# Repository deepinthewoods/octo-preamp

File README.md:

# PCB boards

This repository contains schematics and boards built using the `pcb` command line utility by Diode, using the Zener language and open source compiler

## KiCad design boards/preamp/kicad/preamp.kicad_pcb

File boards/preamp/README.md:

# preamp

## Description

<!-- Brief description of this board -->

## Features

-

## Build Instructions

```bash
pcb build boards/preamp
pcb layout boards/preamp
```

## License

<!-- Add license information -->

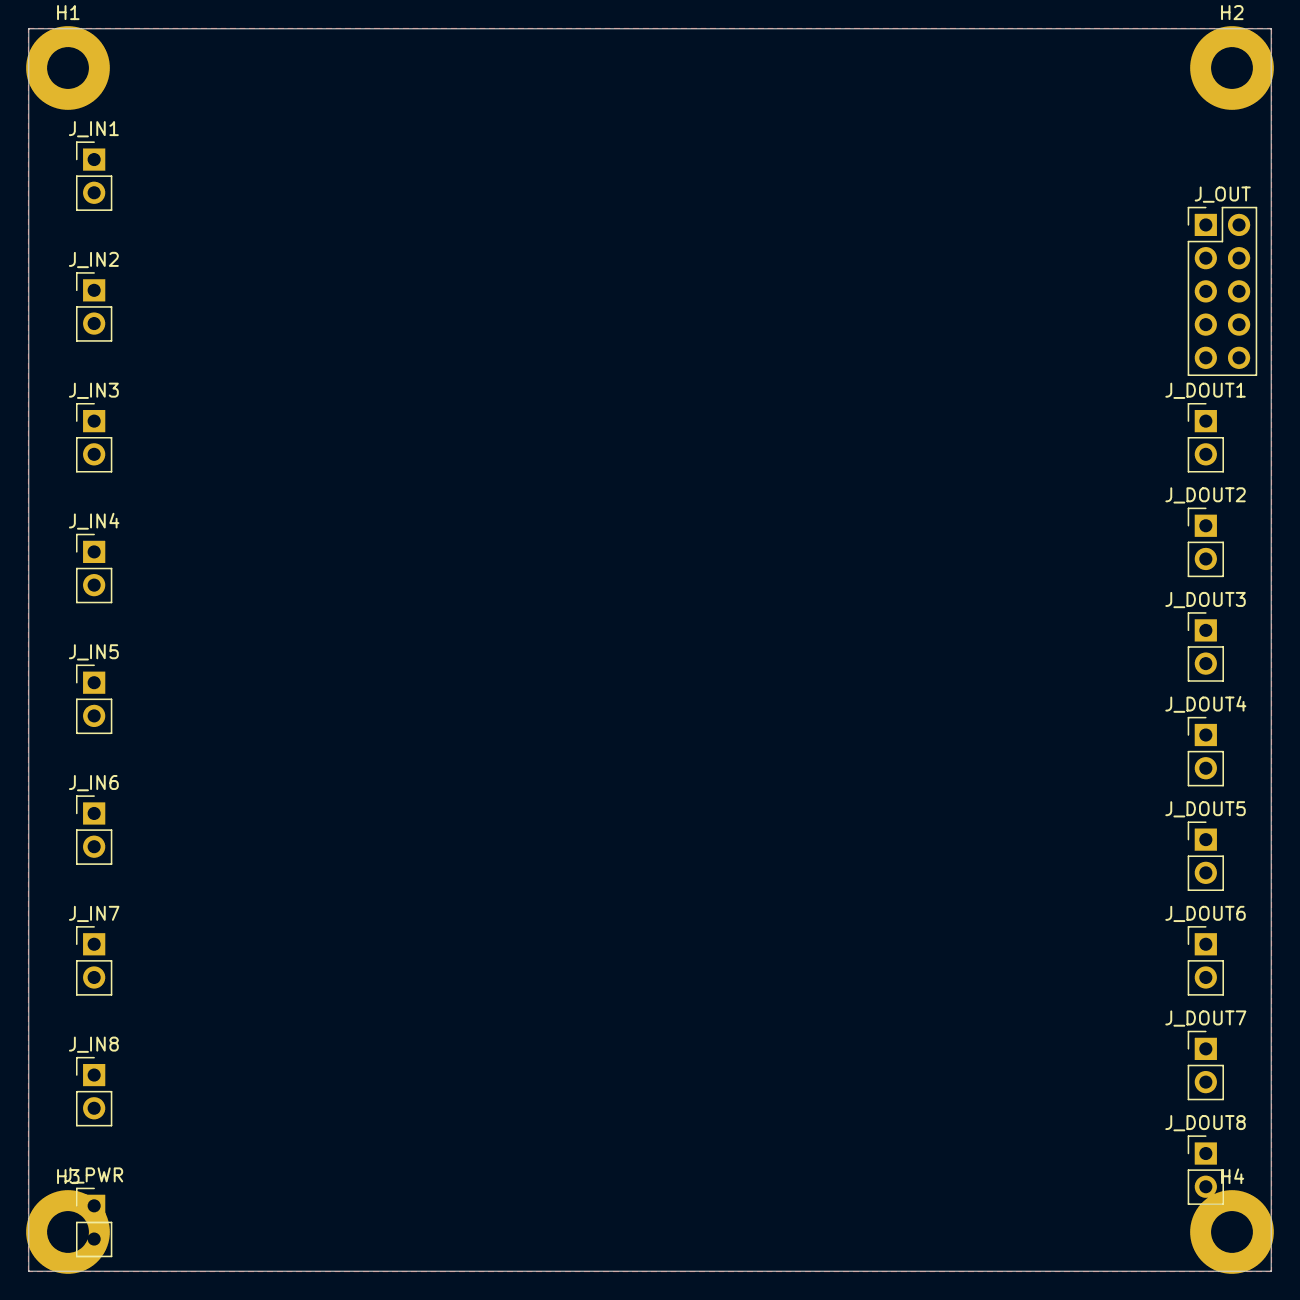
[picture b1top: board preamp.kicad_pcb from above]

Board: 4 copper layers, 95.0 x 95.0 mm, 22 parts (0 on the bottom side), 2 nets, no tracks yet.

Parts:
H1, H2, H3, H4: MountingHole; MountingHole_3.2mm_M3_Pad
J_DOUT1: DOUT_1; PinHeader_1x02_P2.54mm_Vertical
J_DOUT2: DOUT_2; PinHeader_1x02_P2.54mm_Vertical
J_DOUT3: DOUT_3; PinHeader_1x02_P2.54mm_Vertical
J_DOUT4: DOUT_4; PinHeader_1x02_P2.54mm_Vertical
J_DOUT5: DOUT_5; PinHeader_1x02_P2.54mm_Vertical
J_DOUT6: DOUT_6; PinHeader_1x02_P2.54mm_Vertical
J_DOUT7: DOUT_7; PinHeader_1x02_P2.54mm_Vertical
J_DOUT8: DOUT_8; PinHeader_1x02_P2.54mm_Vertical
J_IN1: PICKUP_1; PinHeader_1x02_P2.54mm_Vertical
J_IN2: PICKUP_2; PinHeader_1x02_P2.54mm_Vertical
J_IN3: PICKUP_3; PinHeader_1x02_P2.54mm_Vertical
J_IN4: PICKUP_4; PinHeader_1x02_P2.54mm_Vertical
J_IN5: PICKUP_5; PinHeader_1x02_P2.54mm_Vertical
J_IN6: PICKUP_6; PinHeader_1x02_P2.54mm_Vertical
J_IN7: PICKUP_7; PinHeader_1x02_P2.54mm_Vertical
J_IN8: PICKUP_8; PinHeader_1x02_P2.54mm_Vertical
J_OUT: J_OUT; PinHeader_2x05_P2.54mm_Vertical
J_PWR: J_PWR; PinHeader_1x02_P2.54mm_Vertical

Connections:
AVDD: J_OUT.9, J_PWR.1
GND: H1.1, H2.1, H3.1, H4.1, J_DOUT1.2, J_DOUT2.2, J_DOUT3.2, J_DOUT4.2, J_DOUT5.2, J_DOUT6.2, J_DOUT7.2, J_DOUT8.2, J_IN1.2, J_IN2.2, J_IN3.2, J_IN4.2, J_IN5.2, J_IN6.2, J_IN7.2, J_IN8.2, J_OUT.10, J_PWR.2

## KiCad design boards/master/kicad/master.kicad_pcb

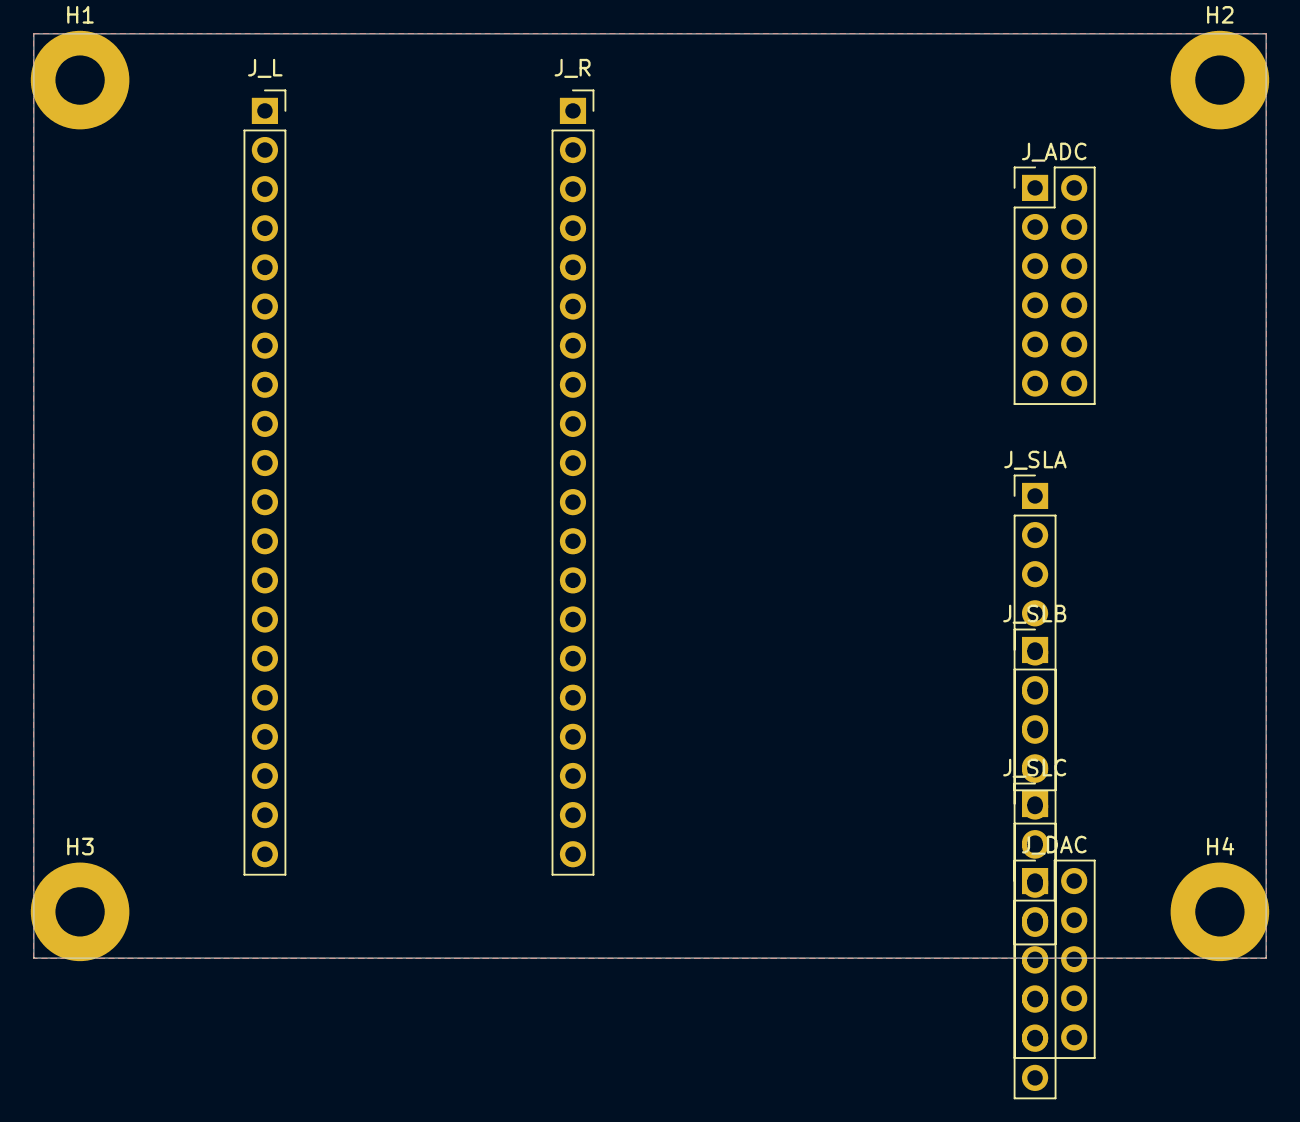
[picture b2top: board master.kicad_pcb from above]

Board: 4 copper layers, 80.0 x 60.0 mm, 11 parts (0 on the bottom side), 8 nets, no tracks yet.

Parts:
H1, H2, H3, H4: MountingHole; MountingHole_3.2mm_M3_Pad
J_ADC: J_ADC; PinHeader_2x06_P2.54mm_Vertical
J_DAC: J_DAC; PinHeader_2x05_P2.54mm_Vertical
J_L: DevKit_Left; PinSocket_1x20_P2.54mm_Vertical
J_R: DevKit_Right; PinSocket_1x20_P2.54mm_Vertical
J_SLA: J_SLAVE_A; PinHeader_1x08_P2.54mm_Vertical
J_SLB: J_SLAVE_B; PinHeader_1x08_P2.54mm_Vertical
J_SLC: J_SLAVE_C; PinHeader_1x08_P2.54mm_Vertical

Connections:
AGND: J_ADC.10, J_DAC.7
AVDD_3V3: J_ADC.8, J_DAC.5
BCLK_OUT: J_SLA.1, J_SLB.1, J_SLC.1
DGND: H1.1, H2.1, H3.1, H4.1, J_ADC.11, J_DAC.8, J_SLA.8, J_SLB.8, J_SLC.8
DVDD_3V3: J_ADC.9, J_DAC.6, J_SLA.7, J_SLB.7, J_SLC.7
LRCK_OUT: J_SLA.2, J_SLB.2, J_SLC.2
RX_SLAVE: J_SLA.5, J_SLB.5, J_SLC.5
TX_SLAVE: J_SLA.4, J_SLB.4, J_SLC.4

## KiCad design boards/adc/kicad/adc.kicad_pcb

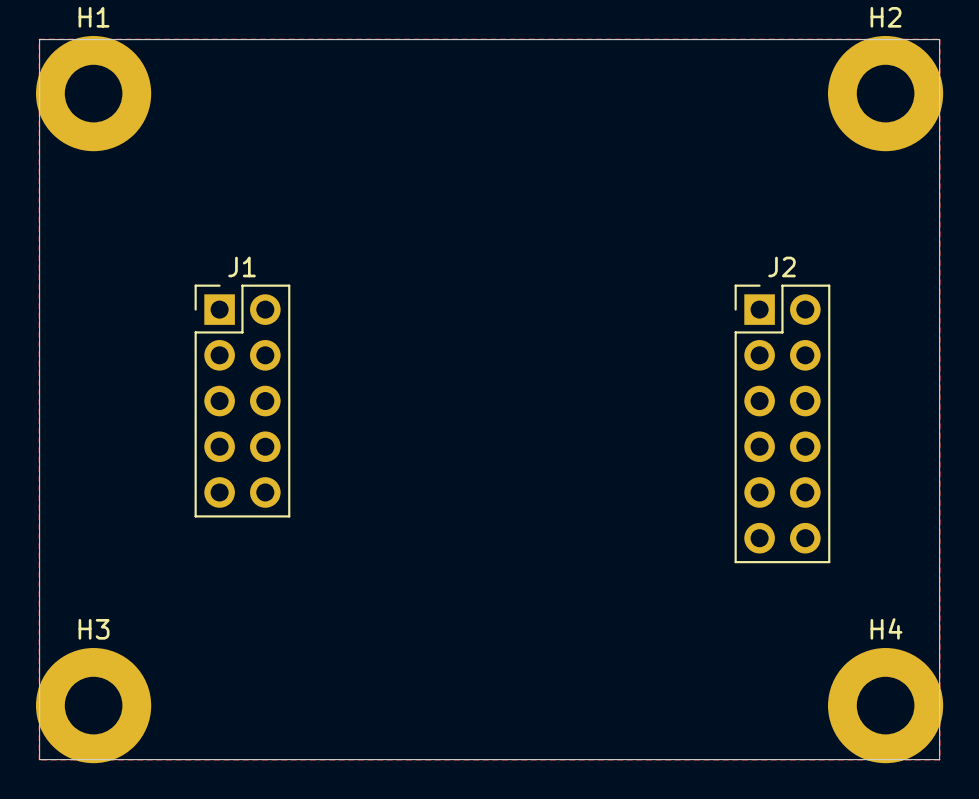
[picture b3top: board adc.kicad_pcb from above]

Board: 4 copper layers, 50.0 x 40.0 mm, 6 parts (0 on the bottom side), 2 nets, no tracks yet.

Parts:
H1, H2, H3, H4: MountingHole; MountingHole_3.2mm_M3_Pad
J1: J_AFE; PinHeader_2x05_P2.54mm_Vertical
J2: J_MASTER; PinHeader_2x06_P2.54mm_Vertical

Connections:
AGND: H1.1, H2.1, H3.1, H4.1, J1.10, J2.10
AVDD: J1.9, J2.8

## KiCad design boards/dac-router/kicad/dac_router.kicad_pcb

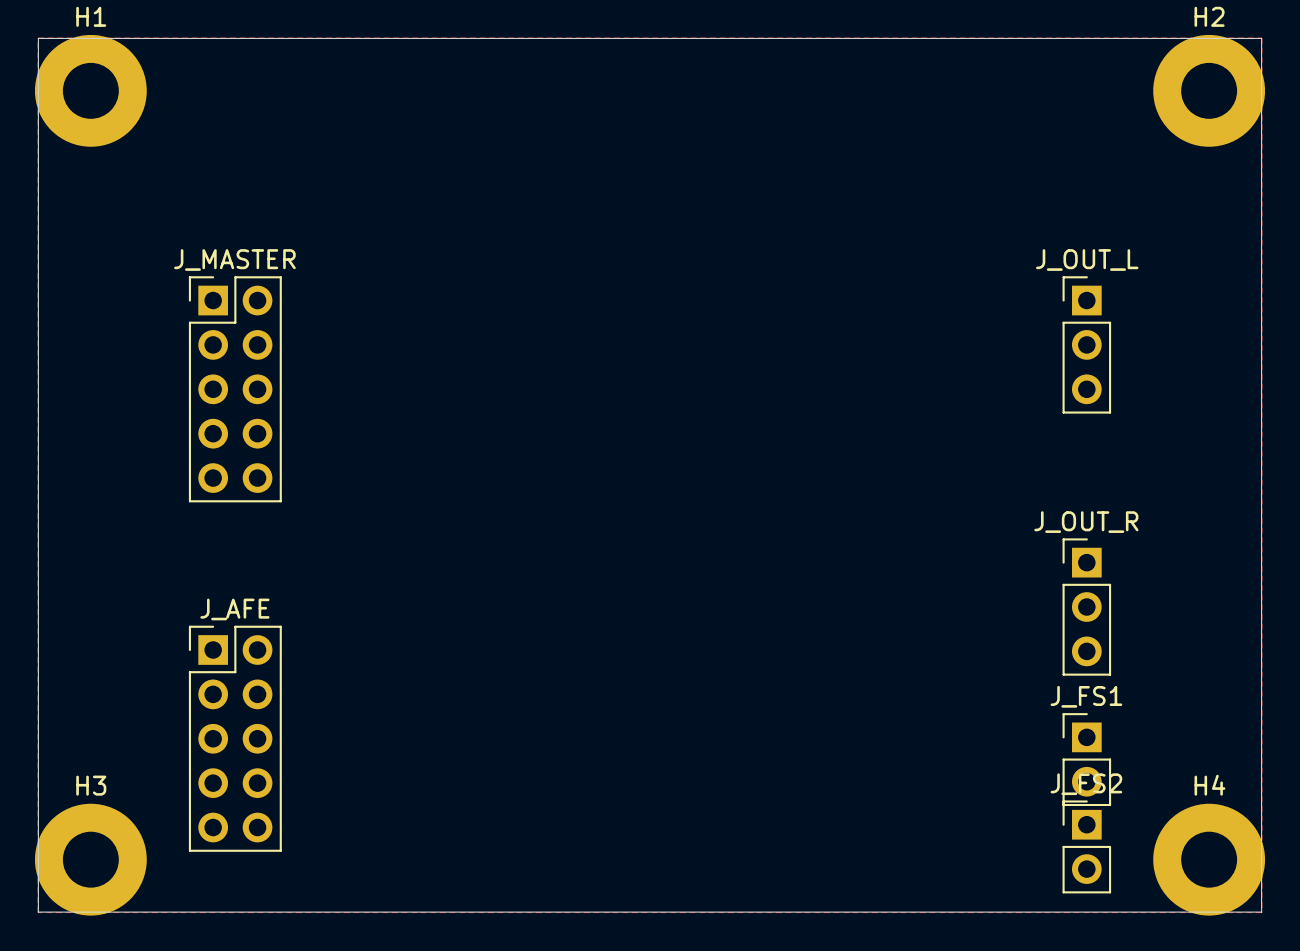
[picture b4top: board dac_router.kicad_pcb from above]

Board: 4 copper layers, 70.0 x 50.0 mm, 10 parts (0 on the bottom side), 2 nets, no tracks yet.

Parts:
H1, H2, H3, H4: MountingHole; MountingHole_3.2mm_M3_Pad
J_AFE: J_AFE; PinHeader_2x05_P2.54mm_Vertical
J_FS1: FS1; PinHeader_1x02_P2.54mm_Vertical
J_FS2: FS2; PinHeader_1x02_P2.54mm_Vertical
J_MASTER: J_MASTER; PinHeader_2x05_P2.54mm_Vertical
J_OUT_L: TRS_L; PinHeader_1x03_P2.54mm_Vertical
J_OUT_R: TRS_R; PinHeader_1x03_P2.54mm_Vertical

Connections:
AGND: H1.1, H2.1, H3.1, H4.1, J_AFE.10, J_MASTER.7, J_OUT_L.3, J_OUT_R.3
AVDD: J_AFE.9, J_MASTER.5

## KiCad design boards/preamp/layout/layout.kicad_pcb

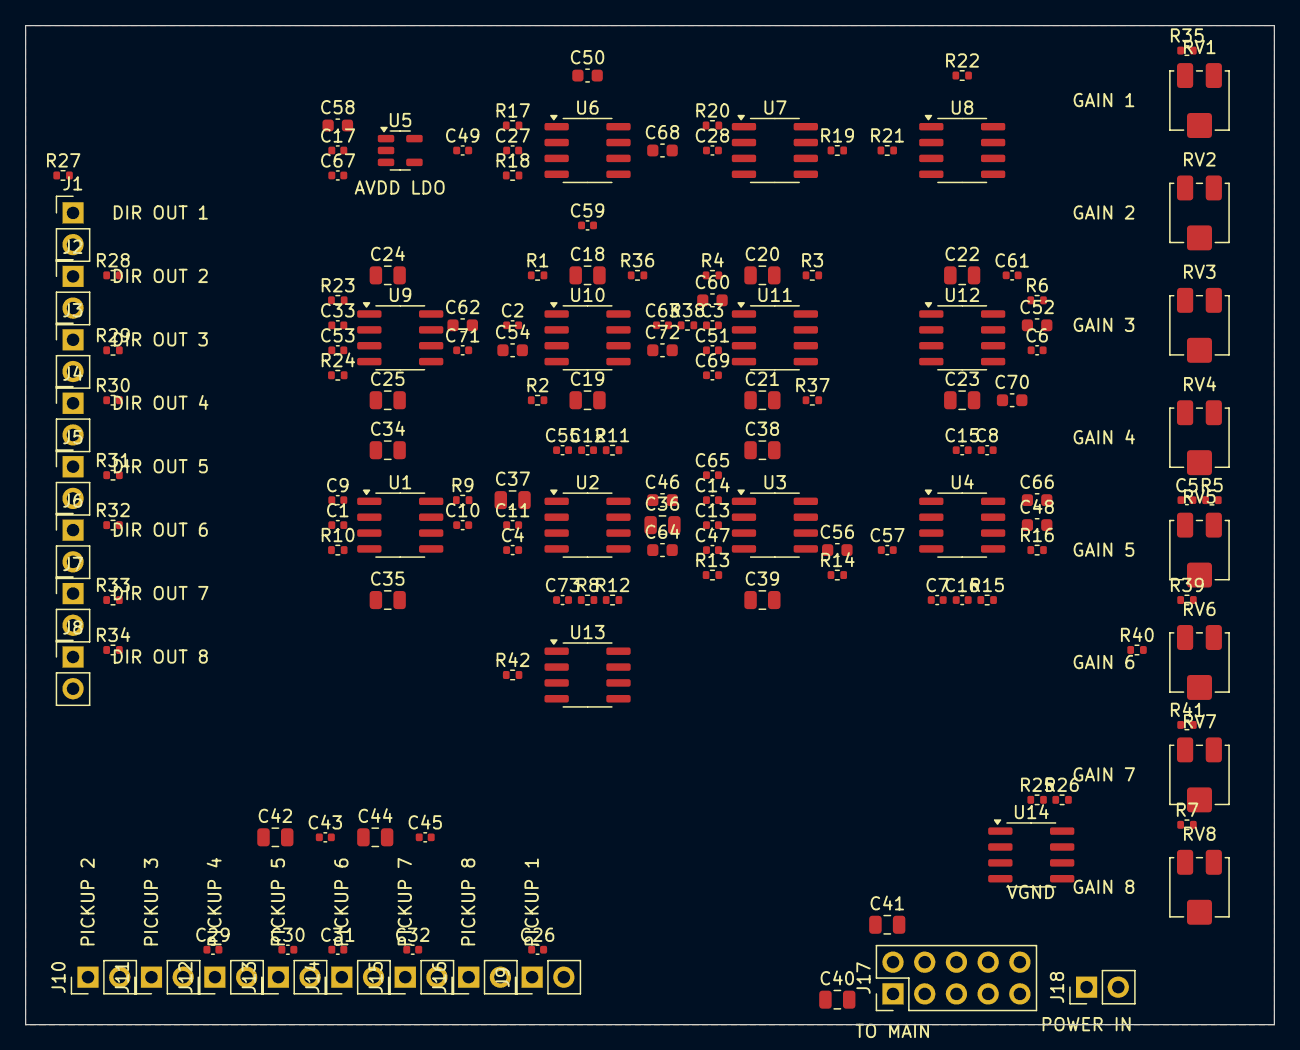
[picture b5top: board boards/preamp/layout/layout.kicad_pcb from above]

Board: 4 copper layers, 100.0 x 80.0 mm, 155 parts (0 on the bottom side), 94 nets, no tracks yet.

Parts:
C1, C2, C3, C4, C5, C6, C7, C8, C9, C10, C11, C12, C13, C14, C15, C16: GCM1555C1H102FA16D; C_0402_1005Metric
C17, C26, C27, C28, C29, C30, C31, C32, C33: GRM1555CYA103GE01D; C_0402_1005Metric
C18, C19, C20, C21, C22, C23, C24, C25, C34, C35, C36, C37, C38, C39, C40, C41, C42: GRM21BZ71E106KE15K; C_0805_2012Metric
C43, C45, C47, C49, C51, C53, C55, C57, C59, C61, C63, C65, C67, C69, C71, C73: GCM155R71H104KE02D; C_0402_1005Metric
C44: capacitor; C_0805_2012Metric
C46, C48, C50, C52, C54, C56, C58, C60, C62, C64, C66, C68, C70, C72: GRM188Z71A106KA73D; C_0603_1608Metric
J1, J2, J3, J4, J5, J6, J7, J8, J9, J10, J11, J12, J13, J14, J15, J16, J18: 61300211121; PinHeader_1x02_P2.54mm_Vertical
J17: 61301021121; PinHeader_2x05_P2.54mm_Vertical
R1, R2, R3, R4, R5, R6, R7, R8, R9, R10, R11, R12, R13, R14, R15, R16: ERJ-2RKF7501X; R_0402_1005Metric
R17, R18, R19, R20, R21, R22, R23, R24: ERJ-2RKF1004X; R_0402_1005Metric
R25, R26: ERJ-2RKF1002X; R_0402_1005Metric
R27, R28, R29, R30, R31, R32, R33, R34: resistor; R_0402_1005Metric
R35, R36, R37, R38, R39, R40, R41, R42: ERJ-2RKF1001X; R_0402_1005Metric
RV1, RV2, RV3, RV4, RV5, RV6, RV7, RV8: 3314J-1-103E; Potentiometer_Bourns_3314J_Vertical
U1, U2, U3, U4, U6, U7, U8, U9, U10, U11, U12, U13, U14: NE5532DR; SOIC-8_3.9x4.9mm_P1.27mm
U5: LP2985-33DBVR; SOT-23-5

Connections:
AAF_NODE_1: C1.1, C9.2, R1.2, R9.1
AAF_NODE_2: C2.1, C10.2, R2.2, R10.1
AAF_NODE_3: C3.1, C11.2, R3.2, R11.1
AAF_NODE_4: C4.1, C12.2, R4.2, R12.1
AAF_NODE_5: C5.1, C13.2, R5.2, R13.1
AAF_NODE_6: C6.1, C14.2, R6.2, R14.1
AAF_NODE_7: C7.1, C15.2, R7.2, R15.1
AAF_NODE_8: C8.1, C16.2, R8.2, R16.1
AAF_OUT_1: R9.2, U1.3
AAF_OUT_2: R10.2, U1.5
AAF_OUT_3: R11.2, U2.3
AAF_OUT_4: R12.2, U2.5
AAF_OUT_5: R13.2, U3.3
AAF_OUT_6: R14.2, U3.5
AAF_OUT_7: R15.2, U4.3
AAF_OUT_8: R16.2, U4.5
AMPLIFIED_1: R1.1, RV1.1, U10.1
AMPLIFIED_2: R2.1, RV2.1, U10.7
AMPLIFIED_3: R3.1, RV3.1, U11.1
AMPLIFIED_4: R4.1, RV4.1, U11.7
AMPLIFIED_5: R5.1, RV5.1, U12.1
AMPLIFIED_6: R6.1, RV6.1, U12.7
AMPLIFIED_7: R7.1, RV7.1, U13.1
AMPLIFIED_8: R8.1, RV8.1, U13.7
AVDD: C46.1, C47.1, C48.1, C49.1, C50.1, C51.1, C52.1, C53.1, C54.1, C55.1, C56.1, C57.1, C58.1, C59.1, C60.1, C61.1, C62.1, C63.1, C64.1, C65.1, C66.1, C67.1, C68.1, C69.1, C70.1, C71.1, C72.1, C73.1, R26.1, U1.8, U2.8, U3.8, U4.8, U5.5, U6.8, U7.8, U8.8, U9.8, U10.8, U11.8, U12.8, U13.8, U14.8
AVDD_BYP: C17.1, U5.4
BUFFERED_1: C18.1, U6.1, U6.2, U10.3
BUFFERED_2: C19.1, U6.6, U6.7, U10.5
BUFFERED_3: C20.1, U7.1, U7.2, U11.3
BUFFERED_4: C21.1, U7.6, U7.7, U11.5
BUFFERED_5: C22.1, U8.1, U8.2, U12.3
BUFFERED_6: C23.1, U8.6, U8.7, U12.5
BUFFERED_7: C24.1, U9.1, U9.2, U13.3
BUFFERED_8: C25.1, U9.6, U9.7, U13.5
COUPLED_1: C26.2, R17.1, U6.3
COUPLED_2: C27.2, R18.1, U6.5
COUPLED_3: C28.2, R19.1, U7.3
COUPLED_4: C29.2, R20.1, U7.5
COUPLED_5: C30.2, R21.1, U8.3
COUPLED_6: C31.2, R22.1, U8.5
COUPLED_7: C32.2, R23.1, U9.3
COUPLED_8: C33.2, R24.1, U9.5
DIRECT_AC_1: C18.2, R27.1
DIRECT_AC_2: C19.2, R28.1
DIRECT_AC_3: C20.2, R29.1
DIRECT_AC_4: C21.2, R30.1
DIRECT_AC_5: C22.2, R31.1
DIRECT_AC_6: C23.2, R32.1
DIRECT_AC_7: C24.2, R33.1
DIRECT_AC_8: C25.2, R34.1
DIRECT_SER_1: J1.1, R27.2
DIRECT_SER_2: J2.1, R28.2
DIRECT_SER_3: J3.1, R29.2
DIRECT_SER_4: J4.1, R30.2
DIRECT_SER_5: J5.1, R31.2
DIRECT_SER_6: J6.1, R32.2
DIRECT_SER_7: J7.1, R33.2
DIRECT_SER_8: J8.1, R34.2
FB_1: R35.2, RV1.2, RV1.3, U10.2
FB_2: R36.2, RV2.2, RV2.3, U10.6
FB_3: R37.2, RV3.2, RV3.3, U11.2
FB_4: R38.2, RV4.2, RV4.3, U11.6
FB_5: R39.2, RV5.2, RV5.3, U12.2
FB_6: R40.2, RV6.2, RV6.3, U12.6
FB_7: R41.2, RV7.2, RV7.3, U13.2
FB_8: R42.2, RV8.2, RV8.3, U13.6
FILTERED_1: C9.1, C34.1, U1.1, U1.2
FILTERED_2: C10.1, C35.1, U1.6, U1.7
FILTERED_3: C11.1, C36.1, U2.1, U2.2
FILTERED_4: C12.1, C37.1, U2.6, U2.7
FILTERED_5: C13.1, C38.1, U3.1, U3.2
FILTERED_6: C14.1, C39.1, U3.6, U3.7
FILTERED_7: C15.1, C40.1, U4.1, U4.2
FILTERED_8: C16.1, C41.1, U4.6, U4.7
GND: C1.2, C2.2, C3.2, C4.2, C5.2, C6.2, C7.2, C8.2, C17.2, C42.2, C43.2, C44.2, C45.2, C46.2, C47.2, C48.2, C49.2, C50.2, C51.2, C52.2, C53.2, C54.2, C55.2, C56.2, C57.2, C58.2, C59.2, C60.2, C61.2, C62.2, C63.2, C64.2, C65.2, C66.2, C67.2, C68.2, C69.2, C70.2, C71.2, C72.2, C73.2, J1.2, J2.2, J3.2, J4.2, J5.2, J6.2, J7.2, J8.2, J9.2, J10.2, J11.2, J12.2, J13.2, J14.2, J15.2, J16.2, J17.10, J18.2, R25.2, U1.4, U2.4, U3.4, U4.4, U5.2, U6.4, U7.4, U8.4, U9.4, U10.4, U11.4, U12.4, U13.4, U14.4
PICKUP_1: C26.1, J9.1
PICKUP_2: C27.1, J10.1
PICKUP_3: C28.1, J11.1
PICKUP_4: C29.1, J12.1
PICKUP_5: C30.1, J13.1
PICKUP_6: C31.1, J14.1
PICKUP_7: C32.1, J15.1
PICKUP_8: C33.1, J16.1
SIGNAL_1: C34.2, J17.1
SIGNAL_2: C35.2, J17.2
SIGNAL_3: C36.2, J17.3
SIGNAL_4: C37.2, J17.4
SIGNAL_5: C38.2, J17.5
SIGNAL_6: C39.2, J17.6
SIGNAL_7: C40.2, J17.7
SIGNAL_8: C41.2, J17.8
VBAT: C42.1, C43.1, J17.9, J18.1, U5.1, U5.3
VGND: C44.1, C45.1, R17.2, R18.2, R19.2, R20.2, R21.2, R22.2, R23.2, R24.2, R35.1, R36.1, R37.1, R38.1, R39.1, R40.1, R41.1, R42.1, U14.1, U14.2
VGND_MID: R25.1, R26.2, U14.3

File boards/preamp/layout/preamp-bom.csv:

Comment,Designator,Footprint,LCSC
GCM1555C1H102FA16D,C1,C_0402_1005Metric,C1546
GCM1555C1H102FA16D,C2,C_0402_1005Metric,C1546
GCM1555C1H102FA16D,C3,C_0402_1005Metric,C1546
GCM1555C1H102FA16D,C4,C_0402_1005Metric,C1546
GCM1555C1H102FA16D,C5,C_0402_1005Metric,C1546
GCM1555C1H102FA16D,C6,C_0402_1005Metric,C1546
GCM1555C1H102FA16D,C7,C_0402_1005Metric,C1546
GCM1555C1H102FA16D,C8,C_0402_1005Metric,C1546
GCM1555C1H102FA16D,C9,C_0402_1005Metric,C1546
GCM1555C1H102FA16D,C10,C_0402_1005Metric,C1546
GCM1555C1H102FA16D,C11,C_0402_1005Metric,C1546
GCM1555C1H102FA16D,C12,C_0402_1005Metric,C1546
GCM1555C1H102FA16D,C13,C_0402_1005Metric,C1546
GCM1555C1H102FA16D,C14,C_0402_1005Metric,C1546
GCM1555C1H102FA16D,C15,C_0402_1005Metric,C1546
GCM1555C1H102FA16D,C16,C_0402_1005Metric,C1546
GRM21BZ71E106KE15K,C17,C_0805_2012Metric,C15850
GRM21BZ71E106KE15K,C18,C_0805_2012Metric,C15850
GRM21BZ71E106KE15K,C19,C_0805_2012Metric,C15850
GRM21BZ71E106KE15K,C20,C_0805_2012Metric,C15850
GRM21BZ71E106KE15K,C21,C_0805_2012Metric,C15850
GRM21BZ71E106KE15K,C22,C_0805_2012Metric,C15850
GRM21BZ71E106KE15K,C23,C_0805_2012Metric,C15850
GRM21BZ71E106KE15K,C24,C_0805_2012Metric,C15850
GRM1555CYA103GE01D,C25,C_0402_1005Metric,C15195
GRM1555CYA103GE01D,C26,C_0402_1005Metric,C15195
GRM1555CYA103GE01D,C27,C_0402_1005Metric,C15195
GRM1555CYA103GE01D,C28,C_0402_1005Metric,C15195
GRM1555CYA103GE01D,C29,C_0402_1005Metric,C15195
GRM1555CYA103GE01D,C30,C_0402_1005Metric,C15195
GRM1555CYA103GE01D,C31,C_0402_1005Metric,C15195
GRM1555CYA103GE01D,C32,C_0402_1005Metric,C15195
GRM21BZ71E106KE15K,C33,C_0805_2012Metric,C15850
GRM21BZ71E106KE15K,C34,C_0805_2012Metric,C15850
GRM21BZ71E106KE15K,C35,C_0805_2012Metric,C15850
GRM21BZ71E106KE15K,C36,C_0805_2012Metric,C15850
GRM21BZ71E106KE15K,C37,C_0805_2012Metric,C15850
GRM21BZ71E106KE15K,C38,C_0805_2012Metric,C15850
GRM21BZ71E106KE15K,C39,C_0805_2012Metric,C15850
GRM21BZ71E106KE15K,C40,C_0805_2012Metric,C15850
47uF 0805,C41,C_0805_2012Metric,C16780
GCM155R71H104KE02D,C42,C_0402_1005Metric,C307331
GRM188Z71A106KA73D,C43,C_0603_1608Metric,C19702
GCM155R71H104KE02D,C44,C_0402_1005Metric,C307331
GRM188Z71A106KA73D,C45,C_0603_1608Metric,C19702
GCM155R71H104KE02D,C46,C_0402_1005Metric,C307331
GRM188Z71A106KA73D,C47,C_0603_1608Metric,C19702
GCM155R71H104KE02D,C48,C_0402_1005Metric,C307331
GRM188Z71A106KA73D,C49,C_0603_1608Metric,C19702
GCM155R71H104KE02D,C50,C_0402_1005Metric,C307331
GRM188Z71A106KA73D,C51,C_0603_1608Metric,C19702
GCM155R71H104KE02D,C52,C_0402_1005Metric,C307331
GRM188Z71A106KA73D,C53,C_0603_1608Metric,C19702
GCM155R71H104KE02D,C54,C_0402_1005Metric,C307331
GRM188Z71A106KA73D,C55,C_0603_1608Metric,C19702
GCM155R71H104KE02D,C56,C_0402_1005Metric,C307331
GRM188Z71A106KA73D,C57,C_0603_1608Metric,C19702
GCM155R71H104KE02D,C58,C_0402_1005Metric,C307331
GRM188Z71A106KA73D,C59,C_0603_1608Metric,C19702
GCM155R71H104KE02D,C60,C_0402_1005Metric,C307331
GRM188Z71A106KA73D,C61,C_0603_1608Metric,C19702
GCM155R71H104KE02D,C62,C_0402_1005Metric,C307331
GRM188Z71A106KA73D,C63,C_0603_1608Metric,C19702
GCM155R71H104KE02D,C64,C_0402_1005Metric,C307331
GRM188Z71A106KA73D,C65,C_0603_1608Metric,C19702
GCM155R71H104KE02D,C66,C_0402_1005Metric,C307331
GRM188Z71A106KA73D,C67,C_0603_1608Metric,C19702
GCM155R71H104KE02D,C68,C_0402_1005Metric,C307331
ERJ-2RKF7501X,R1,R_0402_1005Metric,C25890
ERJ-2RKF7501X,R2,R_0402_1005Metric,C25890
ERJ-2RKF7501X,R3,R_0402_1005Metric,C25890
ERJ-2RKF7501X,R4,R_0402_1005Metric,C25890
ERJ-2RKF7501X,R5,R_0402_1005Metric,C25890
ERJ-2RKF7501X,R6,R_0402_1005Metric,C25890
ERJ-2RKF7501X,R7,R_0402_1005Metric,C25890
ERJ-2RKF7501X,R8,R_0402_1005Metric,C25890
ERJ-2RKF7501X,R9,R_0402_1005Metric,C25890
ERJ-2RKF7501X,R10,R_0402_1005Metric,C25890
ERJ-2RKF7501X,R11,R_0402_1005Metric,C25890
ERJ-2RKF7501X,R12,R_0402_1005Metric,C25890
ERJ-2RKF7501X,R13,R_0402_1005Metric,C25890
ERJ-2RKF7501X,R14,R_0402_1005Metric,C25890
ERJ-2RKF7501X,R15,R_0402_1005Metric,C25890
ERJ-2RKF7501X,R16,R_0402_1005Metric,C25890
ERJ-2RKF1004X,R17,R_0402_1005Metric,C25731
ERJ-2RKF1004X,R18,R_0402_1005Metric,C25731
ERJ-2RKF1004X,R19,R_0402_1005Metric,C25731
ERJ-2RKF1004X,R20,R_0402_1005Metric,C25731
ERJ-2RKF1004X,R21,R_0402_1005Metric,C25731
ERJ-2RKF1004X,R22,R_0402_1005Metric,C25731
ERJ-2RKF1004X,R23,R_0402_1005Metric,C25731
ERJ-2RKF1004X,R24,R_0402_1005Metric,C25731
ERJ-2RKF1002X,R25,R_0402_1005Metric,C25744
ERJ-2RKF1002X,R26,R_0402_1005Metric,C25744
600R 0402,R27,R_0402_1005Metric,C25618
600R 0402,R28,R_0402_1005Metric,C25618
600R 0402,R29,R_0402_1005Metric,C25618
600R 0402,R30,R_0402_1005Metric,C25618
600R 0402,R31,R_0402_1005Metric,C25618
600R 0402,R32,R_0402_1005Metric,C25618
600R 0402,R33,R_0402_1005Metric,C25618
600R 0402,R34,R_0402_1005Metric,C25618
ERJ-2RKF1001X,R35,R_0402_1005Metric,C11702
ERJ-2RKF1001X,R36,R_0402_1005Metric,C11702
ERJ-2RKF1001X,R37,R_0402_1005Metric,C11702
ERJ-2RKF1001X,R38,R_0402_1005Metric,C11702
ERJ-2RKF1001X,R39,R_0402_1005Metric,C11702
ERJ-2RKF1001X,R40,R_0402_1005Metric,C11702
ERJ-2RKF1001X,R41,R_0402_1005Metric,C11702
ERJ-2RKF1001X,R42,R_0402_1005Metric,C11702
NE5532DR,U1,SOIC-8_3.9x4.9mm_P1.27mm,C7426
NE5532DR,U2,SOIC-8_3.9x4.9mm_P1.27mm,C7426
NE5532DR,U3,SOIC-8_3.9x4.9mm_P1.27mm,C7426
NE5532DR,U4,SOIC-8_3.9x4.9mm_P1.27mm,C7426
NE5532DR,U5,SOIC-8_3.9x4.9mm_P1.27mm,C7426
NE5532DR,U6,SOIC-8_3.9x4.9mm_P1.27mm,C7426
NE5532DR,U7,SOIC-8_3.9x4.9mm_P1.27mm,C7426
NE5532DR,U8,SOIC-8_3.9x4.9mm_P1.27mm,C7426
NE5532DR,U9,SOIC-8_3.9x4.9mm_P1.27mm,C7426
NE5532DR,U10,SOIC-8_3.9x4.9mm_P1.27mm,C7426
NE5532DR,U11,SOIC-8_3.9x4.9mm_P1.27mm,C7426
NE5532DR,U12,SOIC-8_3.9x4.9mm_P1.27mm,C7426
NE5532DR,U13,SOIC-8_3.9x4.9mm_P1.27mm,C7426

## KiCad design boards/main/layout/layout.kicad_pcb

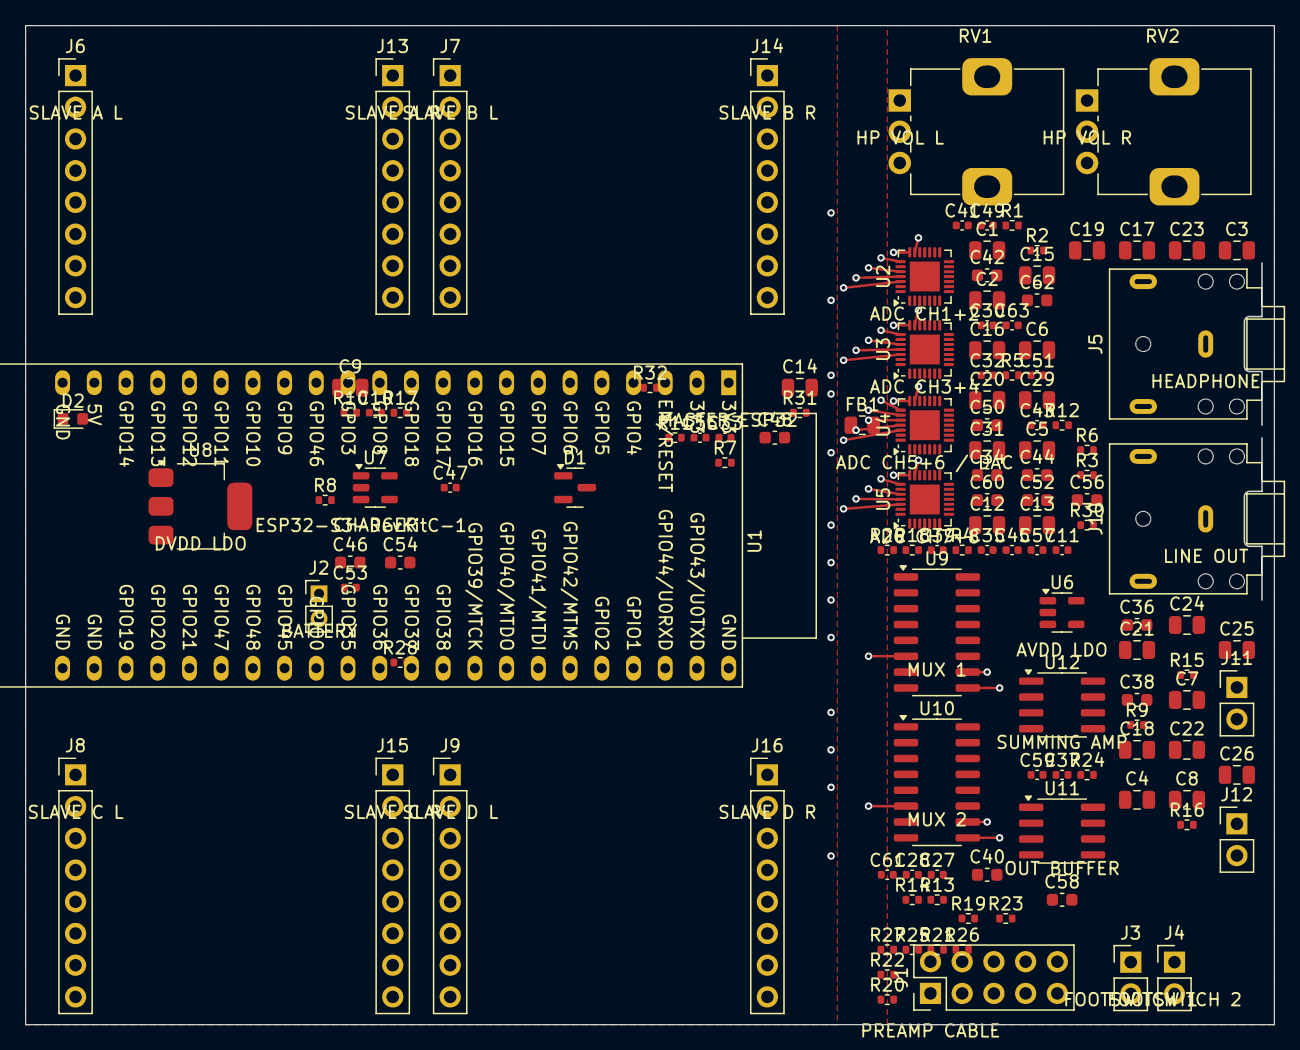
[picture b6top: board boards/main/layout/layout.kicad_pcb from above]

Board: 4 copper layers, 100.0 x 80.0 mm, 128 parts (0 on the bottom side), 94 nets.

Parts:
C1, C2, C3, C4, C5, C6, C7, C8, C12, C13, C15, C16, C17, C18, C19, C20, C21, C22: GRM21BZ71E106KE15K; C_0805_2012Metric
C9, C23, C24, C25, C26, C29, C31: capacitor; C_0805_2012Metric
C10, C27, C28, C30, C32, C33, C35, C37, C39, C41, C43, C45, C47, C49, C51, C53, C55, C57, C59, C61, C63: GCM155R71H104KE02D; C_0402_1005Metric
C11: GRM1555CYA103GE01D; C_0402_1005Metric
C14: GRM21BZ71A226ME15K; C_0805_2012Metric
C34, C36, C38, C40, C42, C44, C46, C48, C50, C52, C54, C56, C58, C60, C62: GRM188Z71A106KA73D; C_0603_1608Metric
D1: BAT54; SOT-23
D2: led; LED_0603_1608Metric
FB1: BLM21PG221SN1D; R_0805_2012Metric
J1: 61301021121; PinHeader_2x05_P2.54mm_Vertical
J2: connector; PinHeader_1x02_P2.00mm_Vertical
J3, J4, J11, J12: 61300211121; PinHeader_1x02_P2.54mm_Vertical
J5, J10: SJ1-3523N; Jack_3.5mm_CUI_SJ1-3523N_Horizontal
J6, J7, J8, J9, J13, J14, J15, J16: 61300811121; PinHeader_1x08_P2.54mm_Vertical
R1, R2, R3, R4, R17: ERJ-2RKF4701X; R_0402_1005Metric
R5, R6, R20, R21, R22, R23, R24, R25, R26, R27, R28, R29, R30: ERJ-2RKF1002X; R_0402_1005Metric
R7, R11, R12: ERJ-2RKF33R0X; R_0402_1005Metric
R8, R9: ERJ-2RKF1201X; R_0402_1005Metric
R10, R13, R14, R15, R16, R18, R19: ERJ-2RKF1001X; R_0402_1005Metric
R31, R32: ERJ-2RKF1003X; R_0402_1005Metric
RV1, RV2: RV09AF-40-20K-B10K; Potentiometer_Alps_RK09K_Single_Vertical
U1: ESP32-S3-DevKitC-1; ESP32-S3-DevKitC
U2, U3, U4, U5: ES8388; QFN-28-1EP_4x4mm_P0.4mm_EP2.4x2.4mm
U6: LP2985-33DBVR; SOT-23-5
U7: MCP73831-2-OTI/OT; SOT-23-5
U8: AP2114H-3.3TRG1; SOT-223-3_TabPin2
U9, U10: CD4052BM96; SOIC-16_3.9x9.9mm_P1.27mm
U11, U12: NE5532DR; SOIC-8_3.9x4.9mm_P1.27mm

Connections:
AD0_HIGH: R5.2, U3.27
AD0_HIGH_2: R6.2, U5.27
ADCDAT_A: U1.8, U2.24
ADCDAT_B: U1.9, U3.24
ADCDAT_C: U1.4, U4.24
ADCDAT_D: U1.29, U5.24
AGND: C1.2, C2.2, C3.2, C4.2, C5.2, C6.2, C7.2, C8.2, C11.2, C15.2, C16.2, C17.2, C18.2, C19.2, C20.2, C21.2, C22.2, C27.2, C28.2, C31.2, C32.2, C34.2, C35.2, C36.2, C37.2, C38.2, C39.2, C40.2, C41.2, C42.2, C43.2, C56.2, C57.2, C58.2, C59.2, C60.2, C61.2, C62.2, C63.2, FB1.1, J1.10, J11.2, J12.2, R29.2, RV1.3, RV2.3, U2.5, U2.27, U2.29, U3.5, U3.29, U4.5, U4.27, U4.29, U5.5, U5.29, U6.2, U9.7, U9.8, U10.1, U10.2, U10.5, U10.7, U10.8, U10.11, U10.13, U10.14, U11.4, U12.4
AVDD: C34.1, C35.1, C36.1, C37.1, C38.1, C39.1, C40.1, C41.1, C42.1, C43.1, C56.1, C57.1, C58.1, C59.1, C60.1, C61.1, C62.1, C63.1, R1.1, R2.1, R3.1, R4.1, R5.1, R6.1, R30.1, U2.4, U2.15, U3.4, U3.15, U4.4, U4.15, U5.4, U5.15, U6.5, U9.16, U10.16, U11.8, U12.8
BCLK: R7.2, U2.21, U3.21, U4.21, U5.21
BCLK_OUT: J6.5, J7.5, J8.5, J9.5, U1.12
BCLK_SRC: R7.1, U1.6
CHARGE_STAT: D2.1, U7.1
DACDAT: U1.19, U4.23
DAC_L_AC: C12.2, U9.14, U10.15
DAC_OUTL: C12.1, U4.7
DAC_OUTR: C13.1, U4.6
DAC_R_AC: C13.2, U9.1, U9.5, U10.4
DGND: C9.2, C10.2, C14.2, C29.2, C30.2, C33.2, C44.2, C45.2, C46.2, C47.2, C48.2, C49.2, C50.2, C51.2, C52.2, C53.2, C54.2, C55.2, FB1.2, J2.2, J13.1, J14.1, J15.1, J16.1, R17.2, R31.2, U1.22, U1.23, U1.24, U1.44, U2.9, U3.9, U4.9, U5.9, U7.2, U8.1
DIN_A: J6.7, U1.16
DIN_B: J7.7, U1.17
DIN_C: J8.7, U1.18
DIN_D: J9.7, U1.20
DVDD: C14.1, C44.1, C45.1, C46.1, C47.1, C48.1, C49.1, C50.1, C51.1, C52.1, C53.1, C54.1, C55.1, J6.1, J6.2, J7.1, J7.2, J8.1, J8.2, J9.1, J9.2, R28.1, U1.1, U1.2, U2.1, U2.8, U2.28, U3.1, U3.8, U3.28, U4.1, U4.8, U4.28, U5.1, U5.8, U5.28, U8.2
DVREF_A1: C15.1, U2.10
DVREF_A2: C16.1, U3.10
DVREF_A3: C17.1, U4.10
DVREF_A4: C18.1, U5.10
DVRP_A1: C19.1, U2.11
DVRP_A2: C20.1, U3.11
DVRP_A3: C21.1, U4.11
DVRP_A4: C22.1, U5.11
EN_SLAVE2: J6.3, U1.38
EN_SLAVE3: J7.3, U1.37
EN_SLAVE4: J8.3, U1.36
EN_SLAVE5: J9.3, U1.34
HP_AC_L: C23.2, RV1.1
HP_AC_R: C24.2, RV2.1
HP_OUTL: C23.1, U4.2
HP_OUTR: C24.1, U4.3
JACK_A_TIP: J11.1, R15.2
JACK_B_TIP: J12.1, R16.2
LED_STAT: D2.2, R10.2
LP2985_BYP: C11.1, U6.4
LRCK: R11.2, U2.22, U3.22, U4.22, U5.22
LRCK_OUT: J6.6, J7.6, J8.6, J9.6, U1.15
LRCK_SRC: R11.1, U1.7
MCLK: R12.2, U2.20, U3.20, U4.20, U5.20
MCLK_SRC: R12.1, U1.5
MUX1_X_FILT: C25.1, C27.1, R13.2, R18.2
MUX1_X_OUT: R18.1, U9.12
MUX1_Y_FILT: C26.1, C28.1, R14.2, R19.2
MUX1_Y_OUT: R19.1, U9.3
MUX2_X_OUT: R13.1, U10.12
MUX2_Y_OUT: R14.1, U10.3
MUX_A: U1.30, U9.10, U10.10
MUX_B: U1.14, U9.9, U10.9
MUX_INH: U1.32, U9.6, U10.6
OUT_A: U9.11, U9.13, U9.15, U11.1, U11.2
OUT_A_AC: C25.2, R15.1
OUT_B: U9.2, U9.4, U11.6, U11.7
OUT_B_AC: C26.2, R16.1
PROG_PIN: R17.1, U7.5
SCL: R1.2, U1.35, U2.26, U3.26
SCL2: R3.2, U1.42, U4.26, U5.26
SDA: R2.2, U1.27, U2.25, U3.25
SDA2: R4.2, U1.43, U4.25, U5.25
SD_FWD_AB: J13.8, J14.8, U1.10
SD_FWD_CD: J15.8, J16.8, U1.11
SIG_CH1: J1.1, R20.1, U2.18
SIG_CH2: J1.2, R21.1, U2.19
SIG_CH3: J1.3, R22.1, U3.18
SIG_CH4: J1.4, R23.1, U3.19
SIG_CH5: J1.5, R24.1, U4.18
SIG_CH6: J1.6, R25.1, U4.19
SIG_CH7: J1.7, R26.1, U5.18
SIG_CH8: J1.8, R27.1, U5.19
SUM_A: R8.2, U11.3, U12.1
SUM_B: R9.2, U11.5, U12.7
SUM_FB_A: R8.1, R20.2, R21.2, R22.2, R23.2, U12.2
SUM_FB_B: R9.1, R24.2, R25.2, R26.2, R27.2, U12.6
UART_SLAVE_TX: J13.7, J14.7, J15.7, J16.7, R28.2
VBAT: C9.1, C10.1, D1.2, J1.9, R32.1, U6.1, U6.3, U8.3
VBAT_MON: C33.1, R31.1, R32.2, U1.33
VBAT_RAW: D1.1, J2.1, U7.3
VBUS: C29.1, C30.1, R10.1, U1.21, U7.4
VGND: C31.1, C32.1, R29.1, R30.2, U12.3, U12.5
VREF_A1: C1.1, U2.14
VREF_A2: C2.1, U3.14
VREF_A3: C3.1, U4.14
VREF_A4: C4.1, U5.14
VRP_A1: C5.1, U2.13
VRP_A2: C6.1, U3.13
VRP_A3: C7.1, U4.13
VRP_A4: C8.1, U5.13

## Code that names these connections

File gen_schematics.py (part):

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    s.add_component("Connector_Generic:Conn_01x08", "J3", "J_MASTER",
                     "Connector_PinHeader_2.54mm:PinHeader_1x08_P2.54mm_Vertical", j3x, j3y)

    # J_LEFT pins: 1=3V3, 2=3V3, 3=RST, 4=GPIO4(NC), 5=BCLK, 6=LRCK, 7=DOUT, 8=GPIO15(NC)
    j1_nets = ["VCC_3V3", "VCC_3V3", "RST", "NC_GPIO4", "BCLK", "LRCK", "DOUT", "NC_GPIO15"]
    for i, net in enumerate(j1_nets):
        if not net.startswith("NC_"):
            s.label_at_pin_1x8(net, j1x, j1y, i+1)
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        if not net.startswith("NC_"):
            s.label_at_pin_1x8(net, j2x, j2y, i+1)

    # J_MASTER pins: 1=BCLK, 2=LRCK, 3=DOUT, 4=UART_RX, 5=UART_TX, 6=RST, 7=VCC_3V3, 8=GND
    j3_nets = ["BCLK", "LRCK", "DOUT", "UART_RX", "UART_TX", "RST", "VCC_3V3", "GND"]
    for i, net in enumerate(j3_nets):
        s.label_at_pin_1x8(net, j3x, j3y, i+1)
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    s.add_component("Connector_Generic:Conn_01x08", "J_OUT_L", "TRS_L",
                     "Connector_PinHeader_2.54mm:PinHeader_1x03_P2.54mm_Vertical", jol_x, jol_y)
    s.label_at_pin_1x8("JACK_L_TIP", jol_x, jol_y, 1)
    s.label_at_pin_1x8("AGND", jol_x, jol_y, 3)

    jor_x, jor_y = 160, 80
    s.add_component("Connector_Generic:Conn_01x08", "J_OUT_R", "TRS_R",
                     "Connector_PinHeader_2.54mm:PinHeader_1x03_P2.54mm_Vertical", jor_x, jor_y)
    s.label_at_pin_1x8("JACK_R_TIP", jor_x, jor_y, 1)
    s.label_at_pin_1x8("AGND", jor_x, jor_y, 3)

    return s.build(lib_symbols)

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    jpwr_x, jpwr_y = 30, 110
    s.add_component("Connector_Generic:Conn_01x08", "J_PWR", "POWER",
                     "Connector_PinHeader_2.54mm:PinHeader_1x02_P2.54mm_Vertical", jpwr_x, jpwr_y)
    s.label_at_pin_1x8("AVDD", jpwr_x, jpwr_y, 1)
    s.label_at_pin_1x8("GND", jpwr_x, jpwr_y, 2)

    return s.build(lib_symbols)
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
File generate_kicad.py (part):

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        "mounting_dia": 3.2,
        "nets": ["", "DGND", "AGND", "VBUS", "VBAT_RAW", "VBAT",
                 "AVDD_3V3", "DVDD_3V3", "USB_DP", "USB_DN", "CC1", "CC2",
                 "CHARGE_STAT", "PROG_PIN", "LED_STAT", "LP2985_BYP",
                 "VBAT_DIV", "VBAT_MON",
                 "MCLK", "BCLK", "LRCK", "ADCDAT_A", "ADCDAT_B",
                 "SDA", "SCL", "TX_SLAVE", "RX_SLAVE",
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
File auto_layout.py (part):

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    # I2C now routed on In2.Cu (separate from I2S) but corridor still needed
    # for I2S clocks, data, and MUX control signals.
    CORRIDOR_X = ox + MOAT_LEFT  # starts at moat left edge (x=75)
    CORRIDOR_W = 14              # extends to x=89, past ES8388 DGND pads and MUX via columns
    CORRIDOR_Y = 25              # above clock fan-out trunks (MCLK trunk at y=26)
    CORRIDOR_H = 52              # down to y=77, below U10 mux (y=70.6) MUX_B pad at y=75
    add_ground_pour(board, "DGND", "In1.Cu", CORRIDOR_X, CORRIDOR_Y, CORRIDOR_W, CORRIDOR_H)
    # AGND: right (analog) section — F.Cu, B.Cu, and In2.Cu
    add_ground_pour(board, "AGND", "F.Cu",  ox + MOAT_RIGHT, oy, bw - MOAT_RIGHT,  bh)
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
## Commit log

2026-03-17 initial zen
2026-03-17 rev 2.1
2026-03-17 2.2 and slave headers moved
2026-03-17 layout changes, main boards smaller
2026-03-17 layout improvement
2026-03-17 layout tweaks
2026-03-17 layout fixes
2026-03-17 layout
2026-03-17 dual ldo
2026-03-18 yout
2026-03-18 ground plane moat etc
2026-03-18 esp32 footprint, layout changes, removed charging usb
2026-03-18 fixes
2026-03-18 layout changes
